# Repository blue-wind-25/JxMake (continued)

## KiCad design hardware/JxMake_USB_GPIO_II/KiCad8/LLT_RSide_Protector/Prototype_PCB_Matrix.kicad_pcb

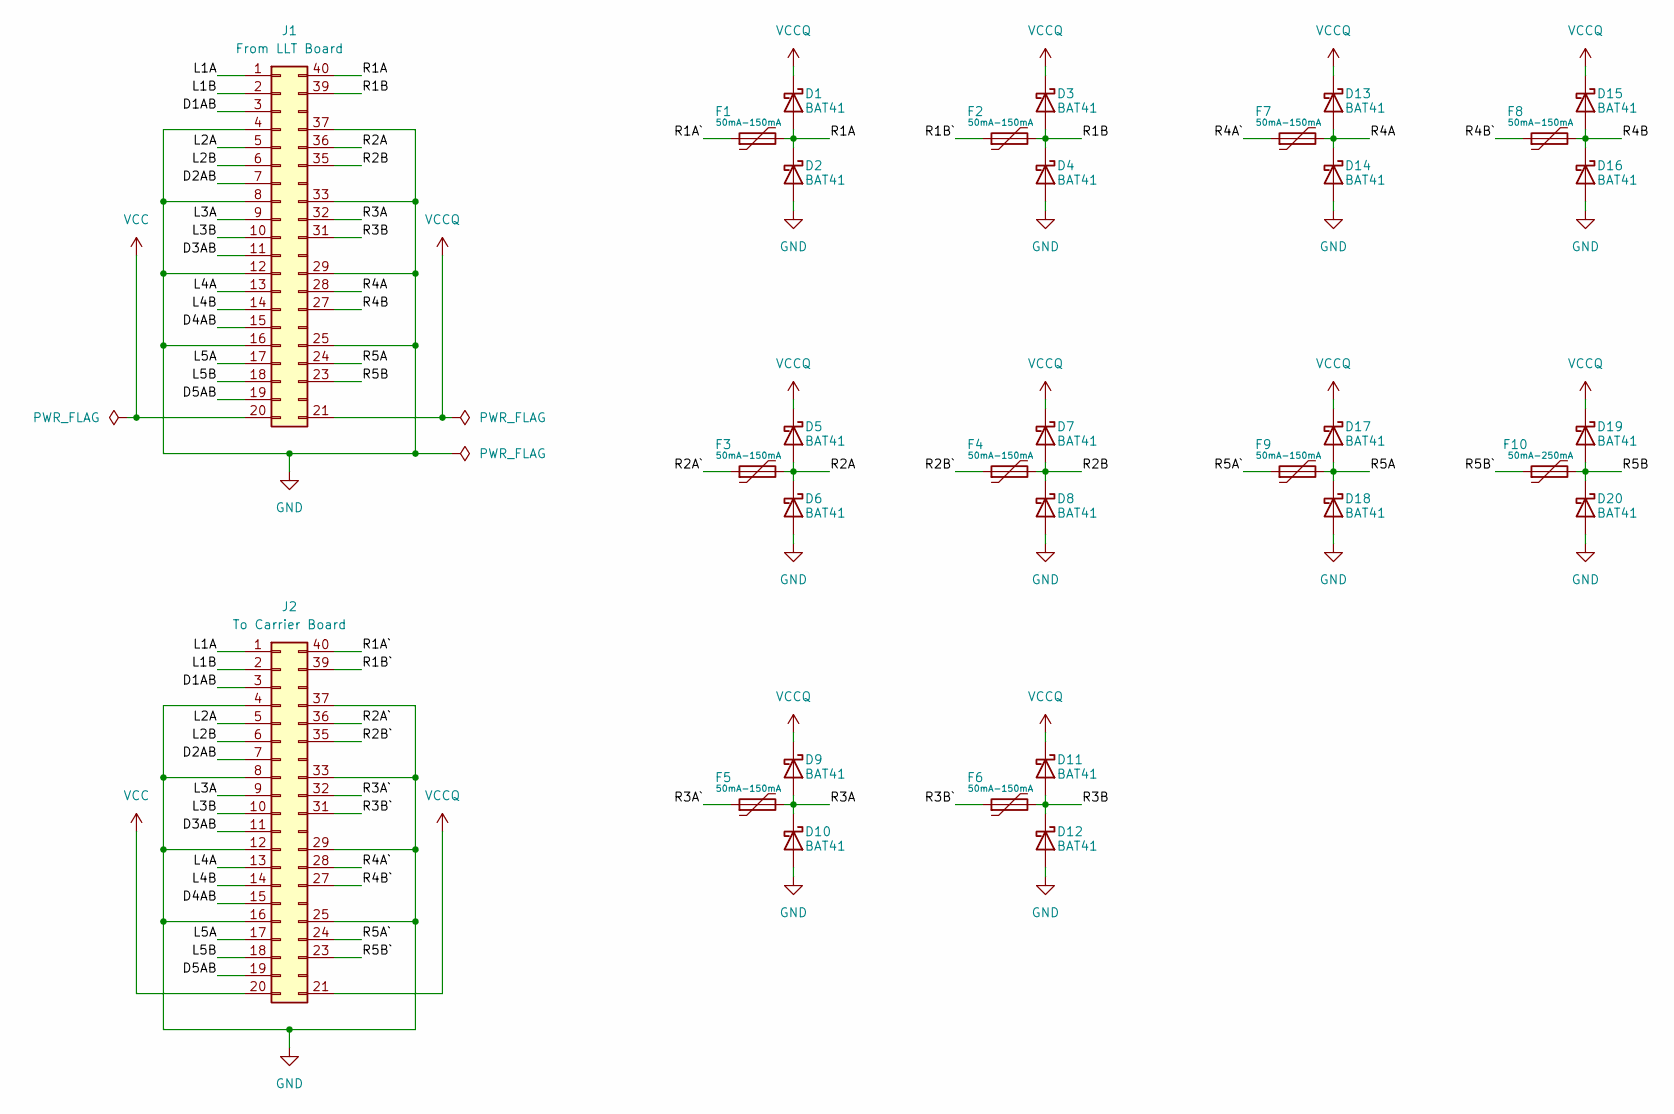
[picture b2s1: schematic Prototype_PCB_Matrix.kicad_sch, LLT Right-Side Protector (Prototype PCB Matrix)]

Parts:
D1, D2, D3, D4, D5, D6, D7, D8, D9, D10, D11, D12, D13, D14, D15, D16, D17, D18, D19, D20: BAT41; D_DO-35_SOD27_P7.62mm_Horizontal
F1, F2, F3, F4, F5, F6, F7, F8, F9: 50mA-150mA; R_1210_3225Metric_Pad1.30x2.65mm_HandSolder
F10: 50mA-250mA; R_1210_3225Metric_Pad1.30x2.65mm_HandSolder
J1: From LLT Board; DIP-40_W25.4mm_LongPads
J2: To Carrier Board; DIP-40_W25.4mm_LongPads

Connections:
/D1AB: J1.3, J2.3
/D2AB: J1.7, J2.7
/D3AB: J1.11, J2.11
/D4AB: J1.15, J2.15
/D5AB: J1.19, J2.19
/L1A: J1.1, J2.1
/L1B: J1.2, J2.2
/L2A: J1.5, J2.5
/L2B: J1.6, J2.6
/L3A: J1.9, J2.9
/L3B: J1.10, J2.10
/L4A: J1.13, J2.13
/L4B: J1.14, J2.14
/L5A: J1.17, J2.17
/L5B: J1.18, J2.18
/R1A: D1.2 (A), D2.1 (K), F1.2, J1.40
/R1A`: F1.1, J2.40
/R1B: D3.2 (A), D4.1 (K), F2.2, J1.39
/R1B`: F2.1, J2.39
/R2A: D5.2 (A), D6.1 (K), F3.2, J1.36
/R2A`: F3.1, J2.36
/R2B: D7.2 (A), D8.1 (K), F4.2, J1.35
/R2B`: F4.1, J2.35
/R3A: D9.2 (A), D10.1 (K), F5.2, J1.32
/R3A`: F5.1, J2.32
/R3B: D11.2 (A), D12.1 (K), F6.2, J1.31
/R3B`: F6.1, J2.31
/R4A: D13.2 (A), D14.1 (K), F7.2, J1.28
/R4A`: F7.1, J2.28
/R4B: D15.2 (A), D16.1 (K), F8.2, J1.27
/R4B`: F8.1, J2.27
/R5A: D17.2 (A), D18.1 (K), F9.2, J1.24
/R5A`: F9.1, J2.24
/R5B: D19.2 (A), D20.1 (K), F10.2, J1.23
/R5B`: F10.1, J2.23
GND: D2.2 (A), D4.2 (A), D6.2 (A), D8.2 (A), D10.2 (A), D12.2 (A), D14.2 (A), D16.2 (A), D18.2 (A), D20.2 (A), J1.4, J1.8, J1.12, J1.16, J1.25, J1.29, J1.33, J1.37, J2.4, J2.8, J2.12, J2.16, J2.25, J2.29, J2.33, J2.37
VCC: J1.20, J2.20
VCCQ: D1.1 (K), D3.1 (K), D5.1 (K), D7.1 (K), D9.1 (K), D11.1 (K), D13.1 (K), D15.1 (K), D17.1 (K), D19.1 (K), J1.21, J2.21

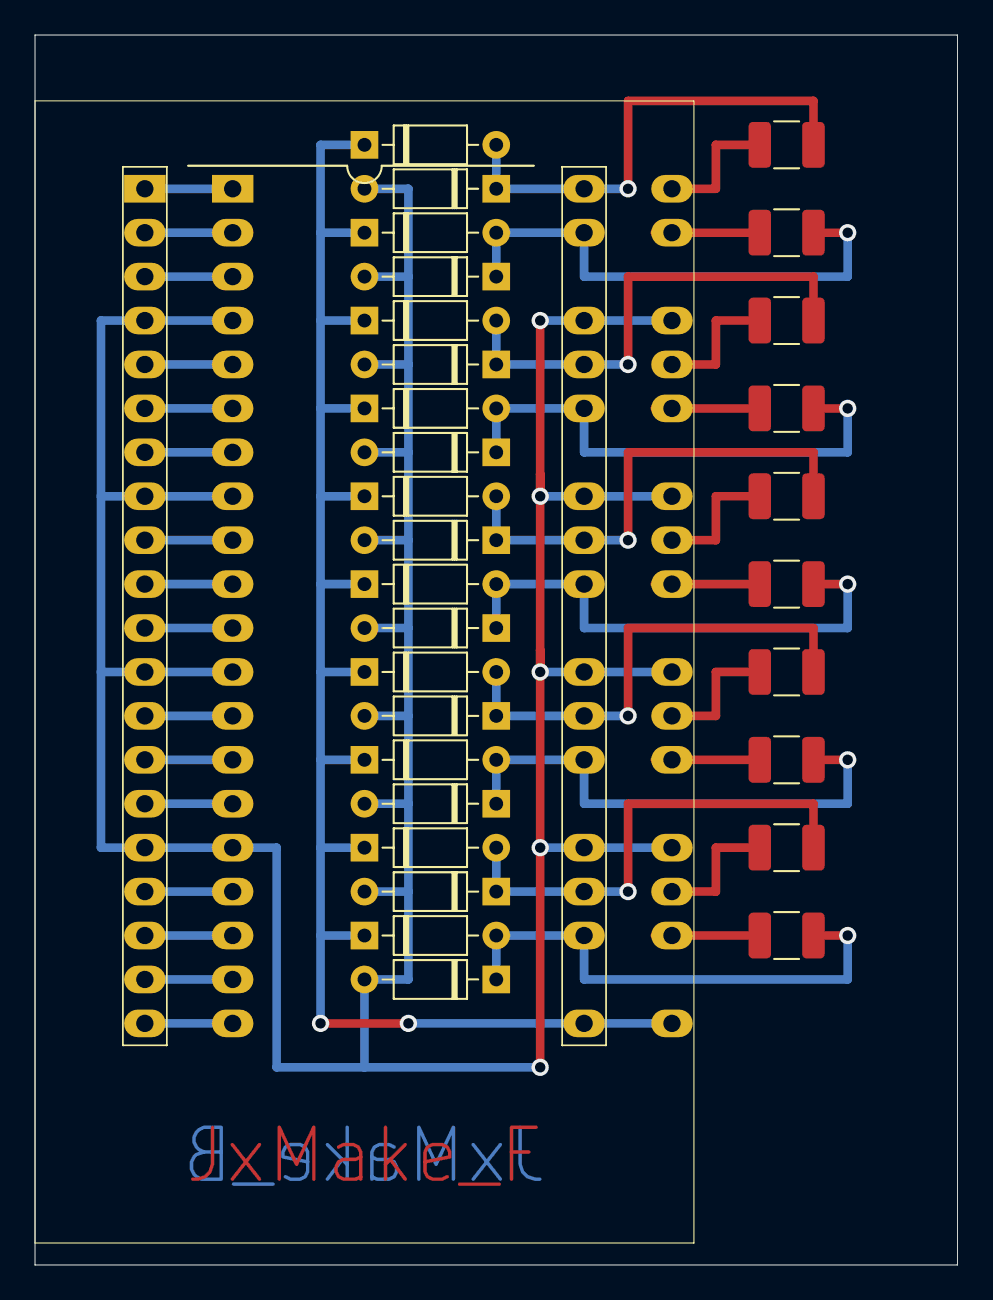
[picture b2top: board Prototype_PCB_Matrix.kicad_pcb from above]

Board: 2 copper layers, 53.3 x 71.1 mm, 32 parts (0 on the bottom side), 38 nets.

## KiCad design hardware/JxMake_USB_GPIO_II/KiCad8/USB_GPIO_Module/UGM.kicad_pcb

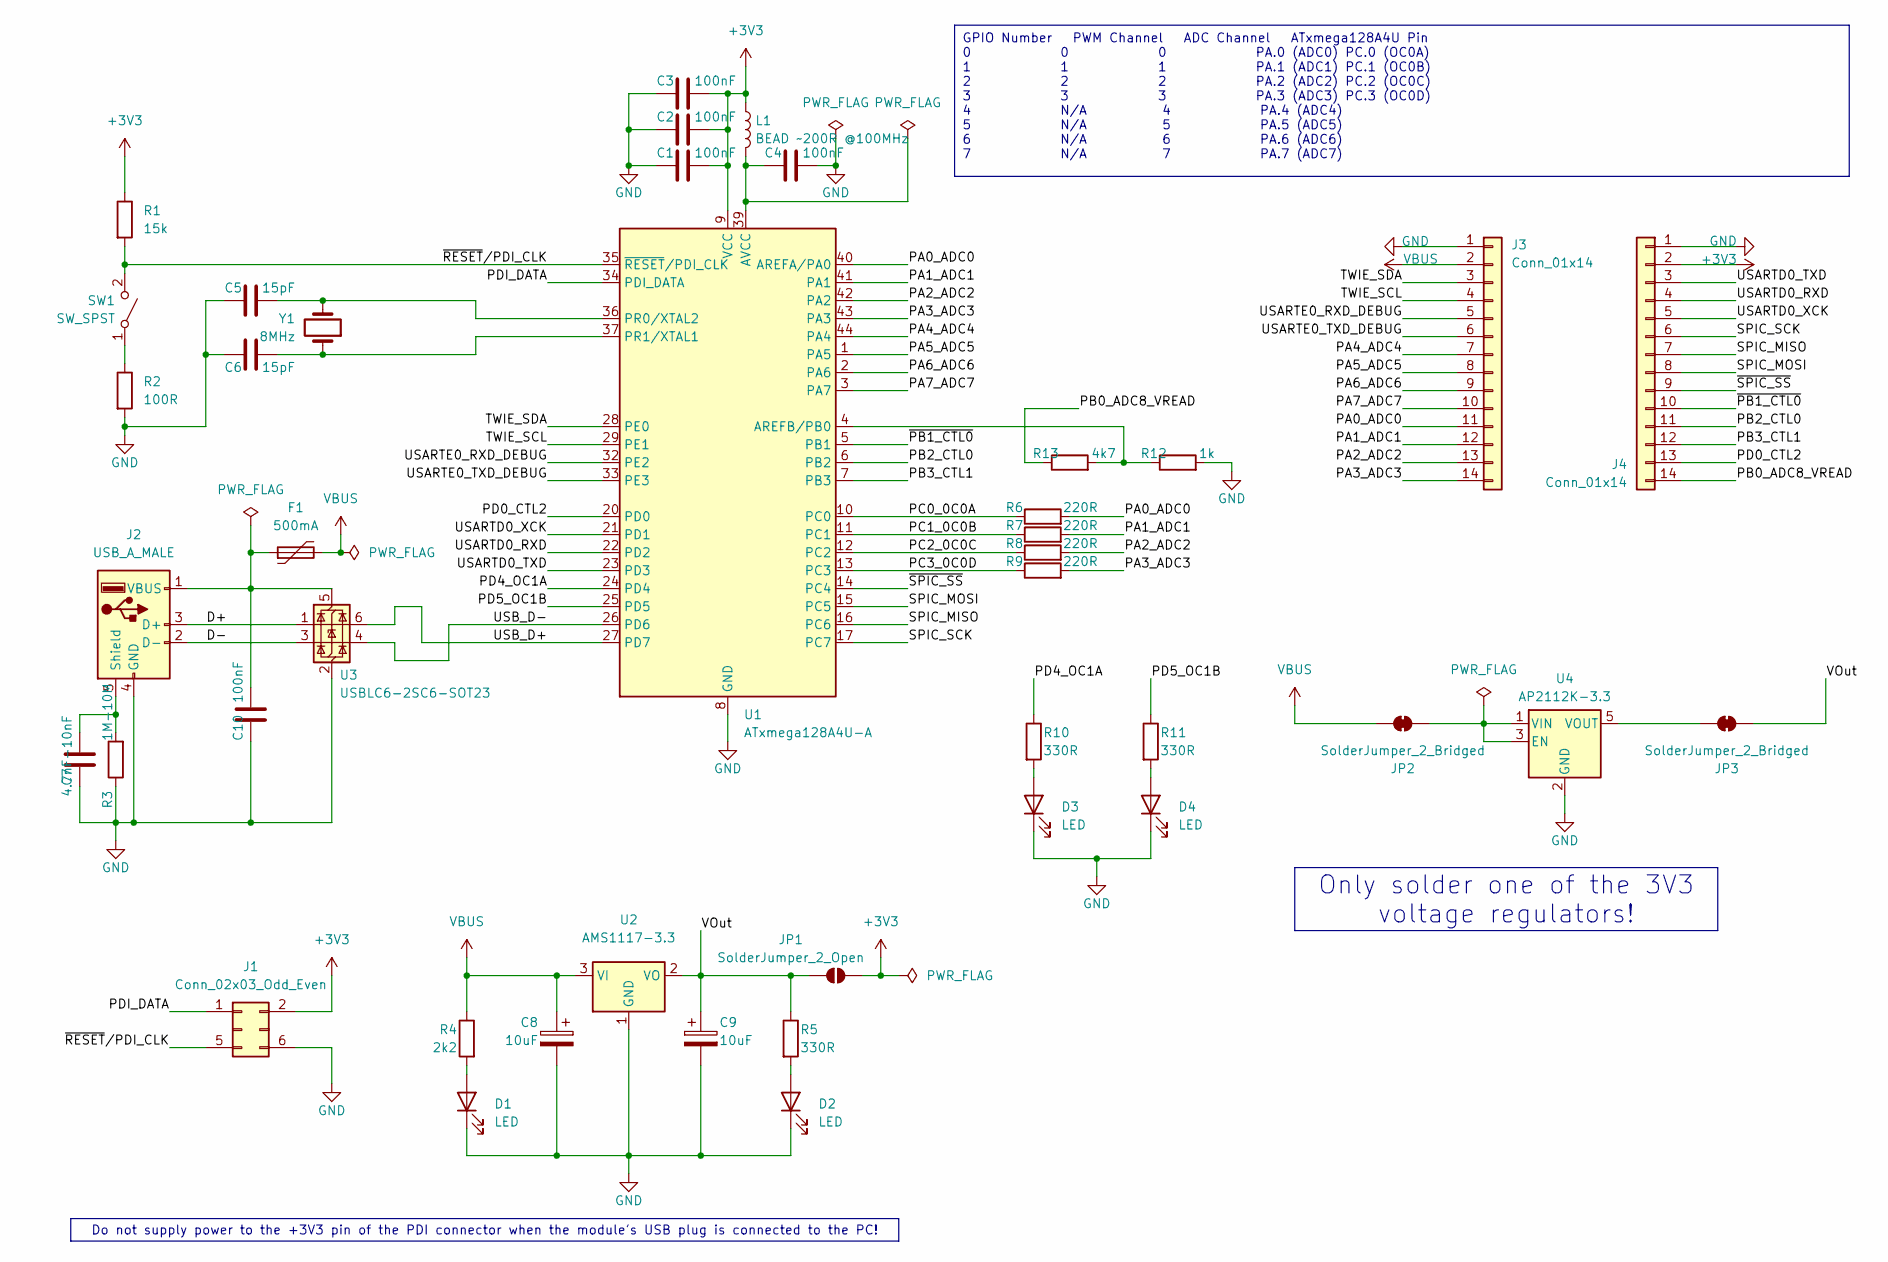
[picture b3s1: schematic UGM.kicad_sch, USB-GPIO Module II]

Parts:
C1, C2, C3, C4, C10: 100nF; C_0805_2012Metric_Pad1.18x1.45mm_HandSolder
C5, C6: 15pF; C_0805_2012Metric_Pad1.18x1.45mm_HandSolder
C7: 4.7nF-10nF; C_0805_2012Metric_Pad1.18x1.45mm_HandSolder
C8, C9: 10uF; CP_EIA-3528-21_Kemet-B_Pad1.50x2.35mm_HandSolder
D1, D2, D3, D4: LED; LED_0805_2012Metric_Pad1.15x1.40mm_HandSolder
F1: 500mA; R_1812_4532Metric_Pad1.30x3.40mm_HandSolder
J1: Conn_02x03_Odd_Even; IDC-Header_2x03_P2.54mm_Vertical
J2: USB_A_MALE; USB_A_CONNFLY_DS1095-WNR0
J3, J4: Conn_01x14; PinHeader_1x14_P2.54mm_Vertical
JP1: SolderJumper_2_Open; SolderJumper-2_P1.3mm_Open_Pad1.0x1.5mm
JP2, JP3: SolderJumper_2_Bridged; SolderJumper-2_P1.3mm_Bridged2Bar_RoundedPad1.0x1.5mm
L1: BEAD ~200R @100MHz; L_0805_2012Metric_Pad1.15x1.40mm_HandSolder
R1: 15k; R_0805_2012Metric_Pad1.20x1.40mm_HandSolder
R2: 100R; R_0805_2012Metric_Pad1.20x1.40mm_HandSolder
R3: 1M-10M; R_0805_2012Metric_Pad1.20x1.40mm_HandSolder
R4: 2k2; R_0805_2012Metric_Pad1.20x1.40mm_HandSolder
R5, R10, R11: 330R; R_0805_2012Metric_Pad1.20x1.40mm_HandSolder
R6, R7, R8, R9: 220R; R_0805_2012Metric_Pad1.20x1.40mm_HandSolder
R12: 1k; R_0805_2012Metric_Pad1.20x1.40mm_HandSolder
R13: 4k7; R_0805_2012Metric_Pad1.20x1.40mm_HandSolder
SW1: SW_SPST; SW_SPST_FSMSM
U1: ATxmega128A4U-A; TQFP-44_10x10mm_P0.8mm
U2: AMS1117-3.3; SOT-223-3_TabPin2
U3: USBLC6-2SC6-SOT23; SOT-23-6
U4: AP2112K-3.3; SOT-23-5
Y1: 8MHz; Crystal_SMD_HC49-SD_HandSoldering

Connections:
+3V3: C1.2, C2.2, C3.2, J1.2, J4.2, JP1.2 (B), L1.1, R1.1, U1.9 (VCC), U1.19 (VCC), U1.31 (VCC)
/D+: J2.3 (D+), U3.1 (I/O1)
/D-: J2.2 (D-), U3.3 (I/O2)
/PA0_ADC0: J3.11, R6.2, U1.40 (AREFA/PA0)
/PA1_ADC1: J3.12, R7.2, U1.41 (PA1)
/PA2_ADC2: J3.13, R8.2, U1.42 (PA2)
/PA3_ADC3: J3.14, R9.2, U1.43 (PA3)
/PA4_ADC4: J3.7, U1.44 (PA4)
/PA5_ADC5: J3.8, U1.1 (PA5)
/PA6_ADC6: J3.9, U1.2 (PA6)
/PA7_ADC7: J3.10, U1.3 (PA7)
/PB0_ADC8_VREAD: J4.14, R13.1
/PB2_CTL0: J4.11, U1.6 (PB2)
/PB3_CTL1: J4.12, U1.7 (PB3)
/PC0_0C0A: R6.1, U1.10 (PC0)
/PC1_0C0B: R7.1, U1.11 (PC1)
/PC2_0C0C: R8.1, U1.12 (PC2)
/PC3_0C0D: R9.1, U1.13 (PC3)
/PD0_CTL2: J4.13, U1.20 (PD0)
/PD4_OC1A: R10.1, U1.24 (PD4)
/PD5_OC1B: R11.1, U1.25 (PD5)
/PDI_DATA: J1.1, U1.34 (PDI_DATA)
/SPIC_MISO: J4.7, U1.16 (PC6)
/SPIC_MOSI: J4.8, U1.15 (PC5)
/SPIC_SCK: J4.6, U1.17 (PC7)
/TWIE_SCL: J3.4, U1.29 (PE1)
/TWIE_SDA: J3.3, U1.28 (PE0)
/USARTD0_RXD: J4.4, U1.22 (PD2)
/USARTD0_TXD: J4.3, U1.23 (PD3)
/USARTD0_XCK: J4.5, U1.21 (PD1)
/USARTE0_RXD_DEBUG: J3.5, U1.32 (PE2)
/USARTE0_TXD_DEBUG: J3.6, U1.33 (PE3)
/USB_D+: U1.27 (PD7), U3.6 (I/O1)
/USB_D-: U1.26 (PD6), U3.4 (I/O2)
/VOut: C9.1, JP1.1 (A), JP3.2 (B), R5.1, U2.2 (VO)
/~PB1_CTL0: J4.10, U1.5 (PB1)
/~RESET/PDI_CLK: J1.5, R1.2, SW1.2 (B), U1.35 (~RESET/PDI_CLK)
/~SPIC_SS: J4.9, U1.14 (PC4)
GND: C1.1, C2.1, C3.1, C4.2, C5.1, C6.1, C7.1, C8.2, C9.2, C10.1, D1.1 (K), D2.1 (K), D3.1 (K), D4.1 (K), J1.6, J2.4 (GND), J3.1, J4.1, R2.2, R3.1, R12.2, U1.8 (GND), U1.18 (GND), U1.30 (GND), U1.38 (GND), U2.1 (GND), U3.2 (GND), U4.2 (GND)
unnamed: D1.2 (A), R4.2
unnamed: D2.2 (A), R5.2
unnamed: D3.2 (A), R10.2
unnamed: D4.2 (A), R11.2
unnamed: C7.2, J2.5 (Shield), R3.2
unnamed: C10.2, F1.1, J2.1 (VBUS), U3.5 (VBUS)
unnamed: JP2.2 (B), U4.1 (VIN), U4.3 (EN)
unnamed: JP3.1 (A), U4.5 (VOUT)
unnamed: R2.1, SW1.1 (A)
unnamed: R12.1, R13.2, U1.4 (AREFB/PB0)
unnamed: C4.1, L1.2, U1.39 (AVCC)
unnamed: C5.2, U1.36 (PR0/XTAL2), Y1.2
unnamed: C6.2, U1.37 (PR1/XTAL1), Y1.1
VBUS: C8.1, F1.2, J3.2, JP2.1 (A), R4.1, U2.3 (VI)

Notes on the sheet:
GPIO Number PWM Channel ADC Channel ATxmega128A4U Pin 0 0 0 PA.0 (ADC0) PC.0 (OC0A) 1 1 1 PA.1 (ADC1) PC.1 (OC0B) 2 2 2 PA.2 (ADC2) PC.2 (OC0C) 3 3 3 PA.3 (ADC3) PC.3 (OC0D) 4 N/A 4 PA.4 (ADC4) 5 N/A 5 PA.5 (ADC5) 6 N/A 6 PA.6 (ADC6) 7 N/A 7 PA.7 (ADC7)
Do not supply power to the +3V3 pin of the PDI connector when the module's USB plug is connected to the PC!
Only solder one of the 3V3 voltage regulators!

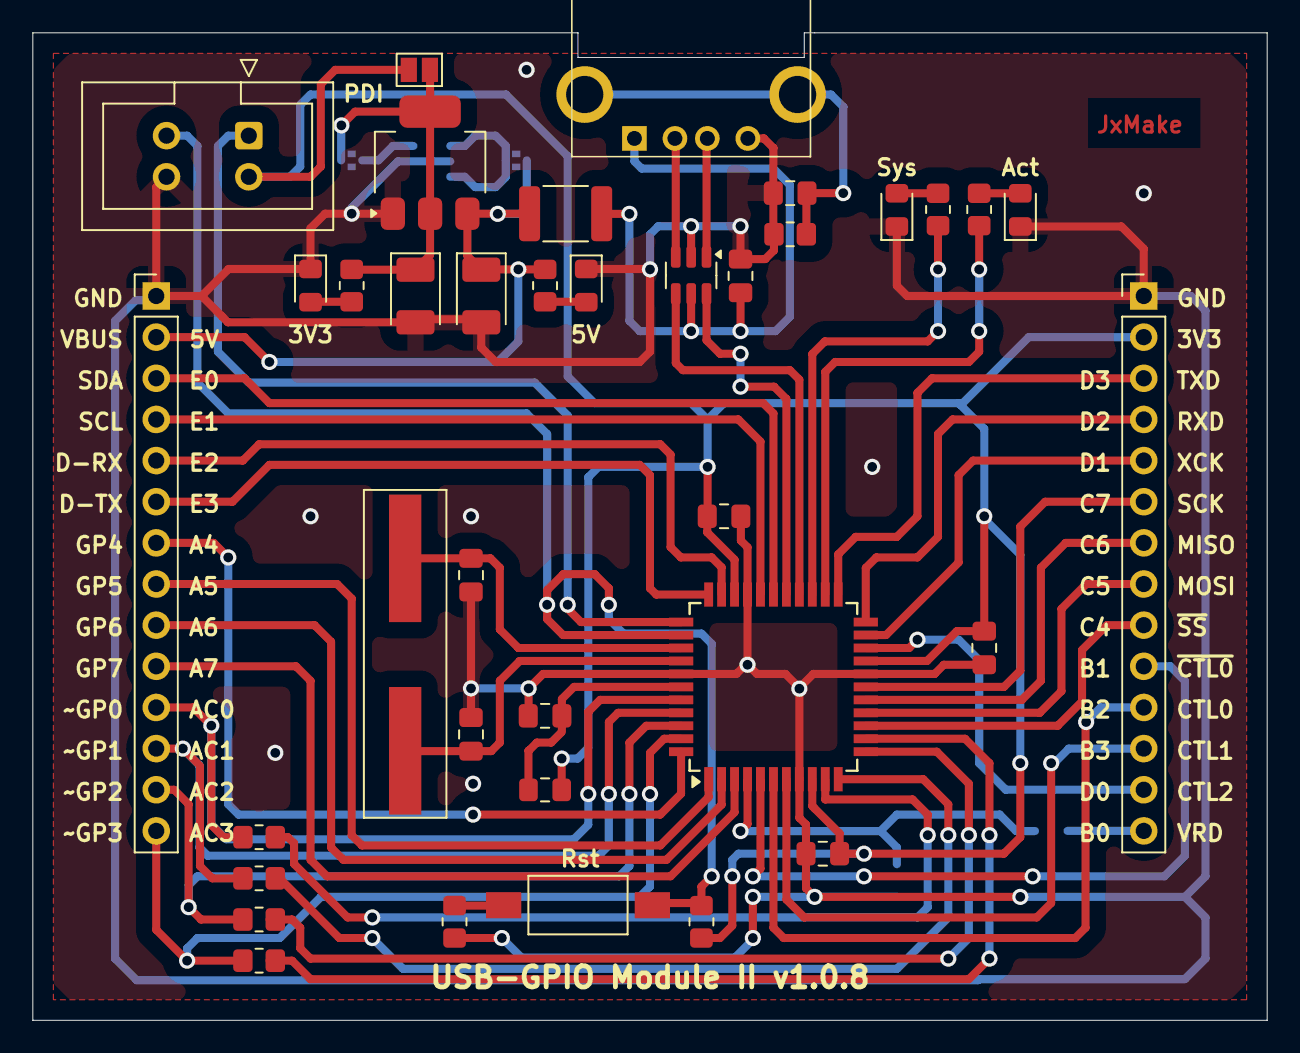
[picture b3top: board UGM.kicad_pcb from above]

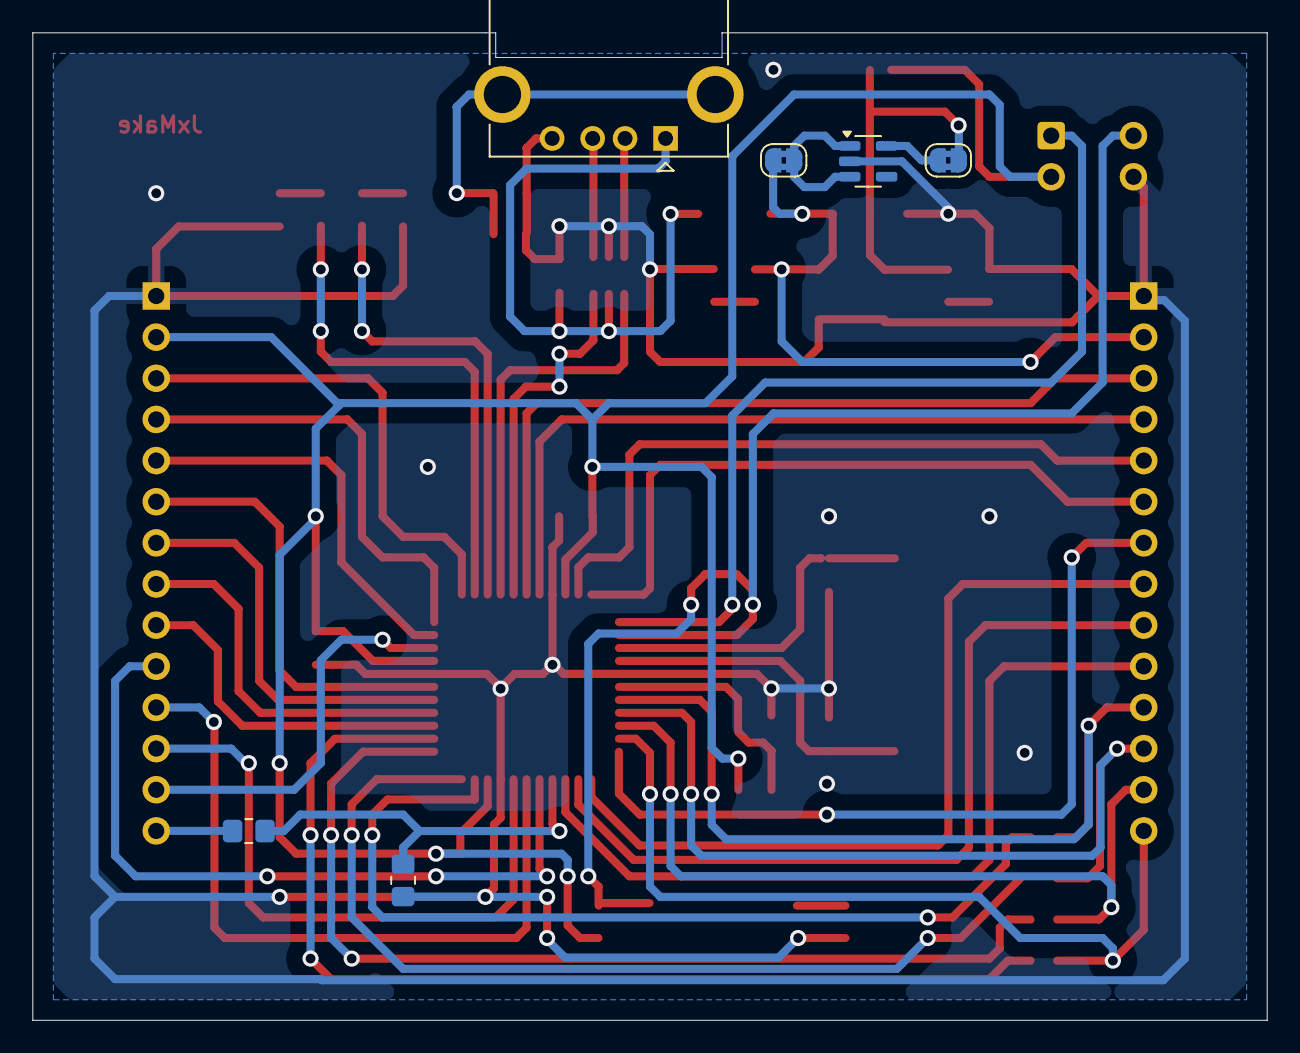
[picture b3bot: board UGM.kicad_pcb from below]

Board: 2 copper layers, 76.2 x 61.0 mm, 42 parts (6 on the bottom side), 53 nets.

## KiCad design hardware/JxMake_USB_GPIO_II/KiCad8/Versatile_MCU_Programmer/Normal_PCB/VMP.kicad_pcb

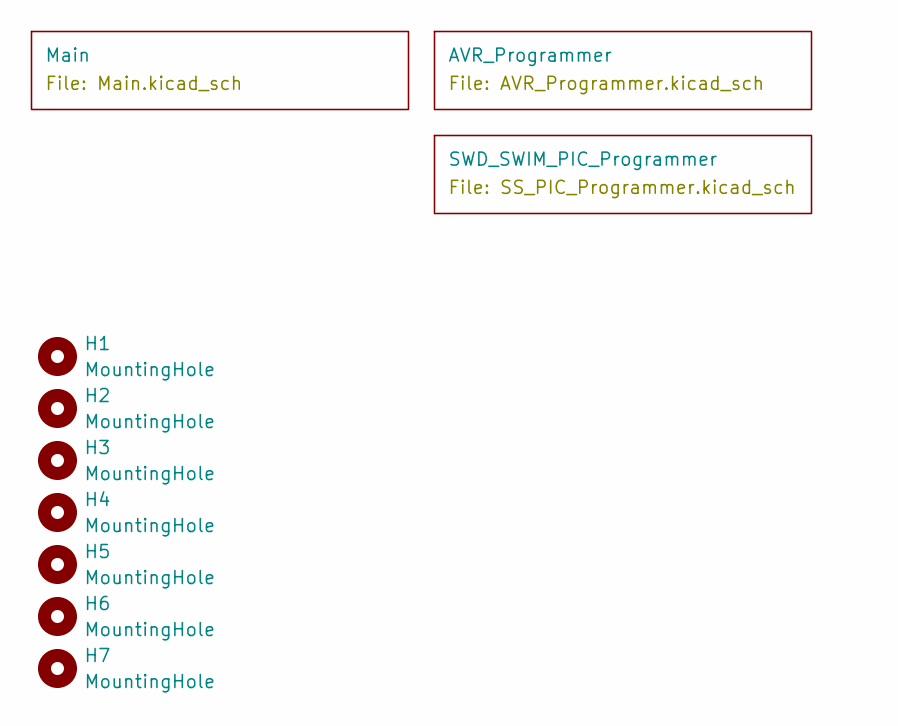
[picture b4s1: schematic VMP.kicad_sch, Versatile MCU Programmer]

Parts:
H1, H2, H3, H4, H5, H6, H7: MountingHole; MountingHole_3.2mm_M3

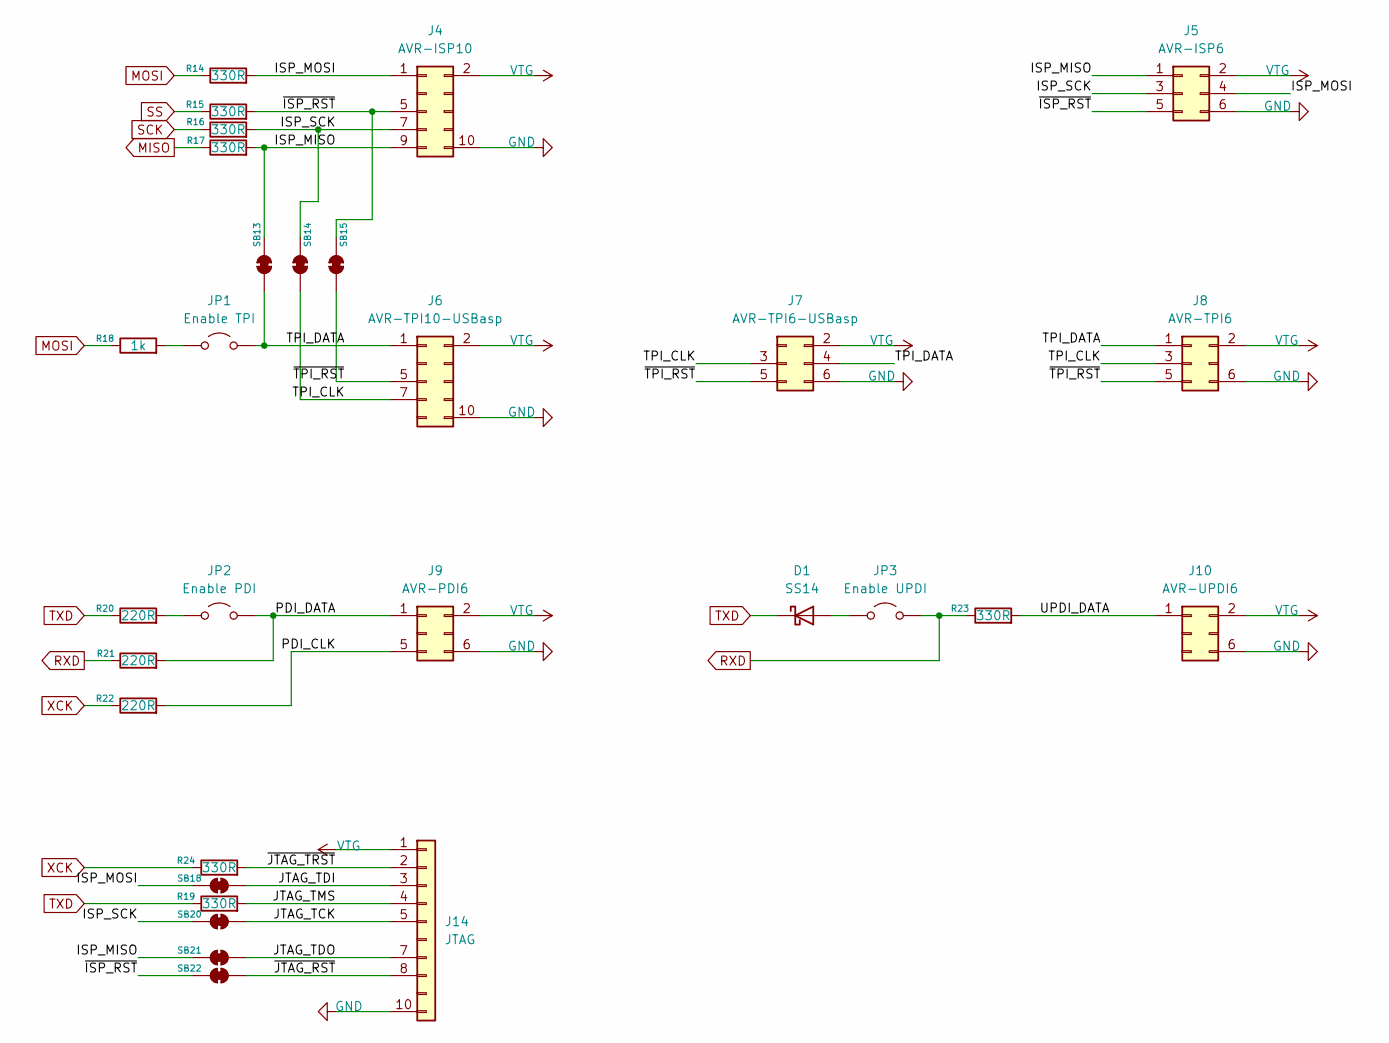
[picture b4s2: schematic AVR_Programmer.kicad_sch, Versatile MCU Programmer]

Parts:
D1: SS14; D_SMA
J4: AVR-ISP10; IDC-Header_2x05_P2.54mm_Vertical
J5: AVR-ISP6; IDC-Header_2x03_P2.54mm_Vertical
J6: AVR-TPI10-USBasp; IDC-Header_2x05_P2.54mm_Vertical
J7: AVR-TPI6-USBasp; IDC-Header_2x03_P2.54mm_Vertical
J8: AVR-TPI6; IDC-Header_2x03_P2.54mm_Vertical
J9: AVR-PDI6; IDC-Header_2x03_P2.54mm_Vertical
J10: AVR-UPDI6; IDC-Header_2x03_P2.54mm_Vertical
J14: JTAG; PinSocket_1x10_P2.54mm_Horizontal
JP1: Enable TPI; PinHeader_1x02_P2.54mm_Vertical
JP2: Enable PDI; PinHeader_1x02_P2.54mm_Vertical
JP3: Enable UPDI; PinHeader_1x02_P2.54mm_Vertical
R14, R15, R16, R17, R19, R23, R24: 330R; R_0805_2012Metric_Pad1.20x1.40mm_HandSolder
R18: 1k; R_0805_2012Metric_Pad1.20x1.40mm_HandSolder
R20, R21, R22: 220R; R_0805_2012Metric_Pad1.20x1.40mm_HandSolder
SB13, SB14, SB15, SB18, SB20, SB21, SB22: Jumper_2_Small_Bridged; SolderJumper-2_P1.3mm_Bridged_Pad1.0x1.5mm

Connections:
/AVR_Programmer/ISP_MISO: J4.9, J5.1, R17.2, SB13.1 (A), SB21.1 (A)
/AVR_Programmer/ISP_MOSI: J4.1, J5.4, R14.2, SB18.1 (A)
/AVR_Programmer/ISP_SCK: J4.7, J5.3, R16.2, SB14.1 (A), SB20.1 (A)
/AVR_Programmer/JTAG_TCK: J14.5, SB20.2 (B)
/AVR_Programmer/JTAG_TDI: J14.3, SB18.2 (B)
/AVR_Programmer/JTAG_TDO: J14.7, SB21.2 (B)
/AVR_Programmer/JTAG_TMS: J14.4, R19.2
/AVR_Programmer/PDI_CLK: J9.5, R22.2
/AVR_Programmer/PDI_DATA: J9.1, JP2.2 (B), R21.2
/AVR_Programmer/TPI_CLK: J6.7, J7.3, J8.3, SB14.2 (B)
/AVR_Programmer/TPI_DATA: J6.1, J7.4, J8.1, JP1.2 (B), SB13.2 (B)
/AVR_Programmer/UPDI_DATA: J10.1, R23.2
/AVR_Programmer/~ISP_RST: J4.5, J5.5, R15.2, SB15.1 (A), SB22.1 (A)
/AVR_Programmer/~JTAG_RST: J14.8, SB22.2 (B)
/AVR_Programmer/~JTAG_TRST: J14.2, R24.2
/AVR_Programmer/~TPI_RST: J6.5, J7.5, J8.5, SB15.2 (B)
GND: J4.10, J5.6, J6.10, J7.6, J8.6, J9.6, J10.6, J14.10; also elsewhere on the board
MISO: R17.1; also elsewhere on the board
MOSI: R14.1, R18.1; also elsewhere on the board
unnamed: D1.2 (A), JP3.1 (A)
unnamed: JP1.1 (A), R18.2
unnamed: JP2.1 (A), R20.2
RXD: JP3.2 (B), R21.1, R23.1; also elsewhere on the board
SCK: R16.1; also elsewhere on the board
SS: R15.1; also elsewhere on the board
TXD: D1.1 (K), R19.1, R20.1; also elsewhere on the board
VTG: J4.2, J5.2, J6.2, J7.2, J8.2, J9.2, J10.2, J14.1; also elsewhere on the board
XCK: R22.1, R24.1; also elsewhere on the board

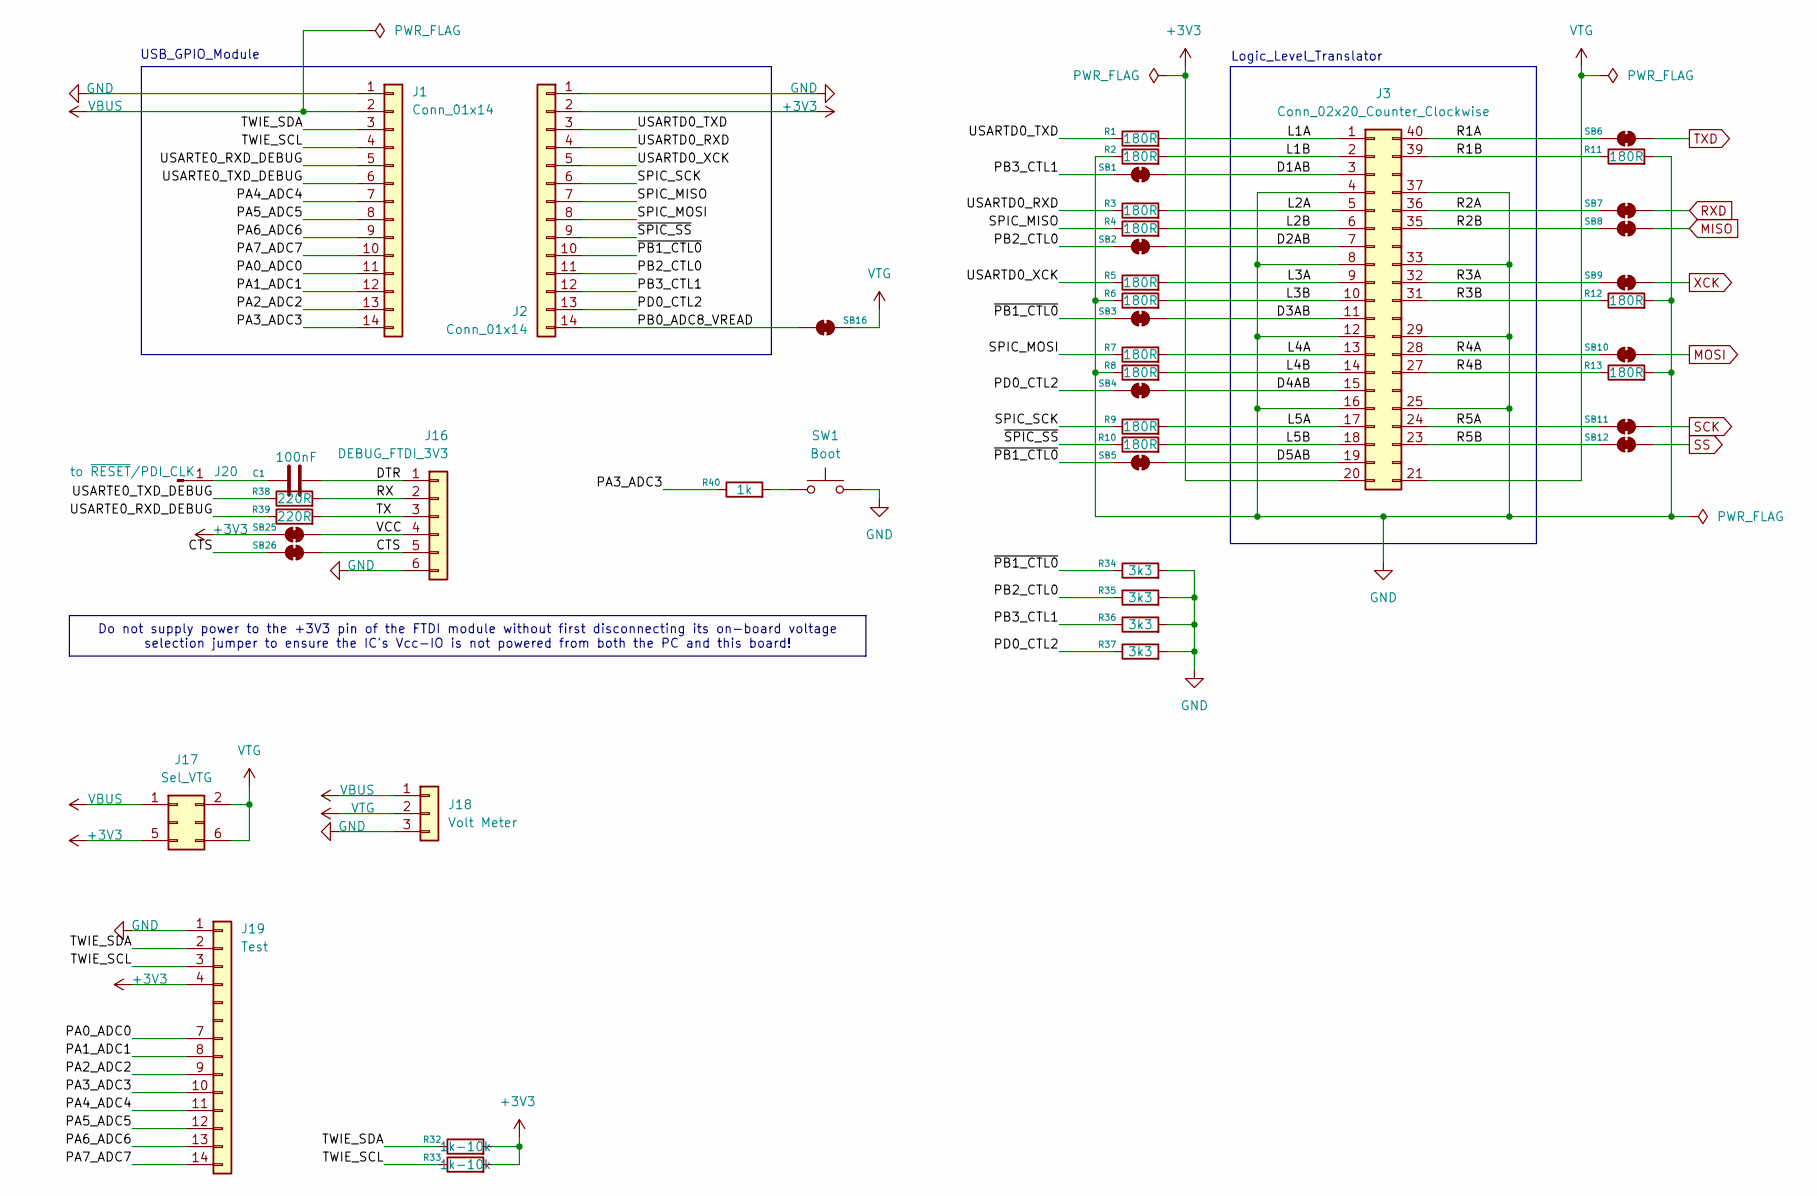
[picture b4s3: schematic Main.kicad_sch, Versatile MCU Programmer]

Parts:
C1: 100nF; C_0805_2012Metric_Pad1.18x1.45mm_HandSolder
J1, J2: Conn_01x14; PinHeader_1x14_P2.54mm_Vertical
J3: Conn_02x20_Counter_Clockwise; DIP-40_W25.4mm_LongPads
J16: DEBUG_FTDI_3V3; PinSocket_1x06_P2.54mm_Horizontal
J17: Sel_VTG; PinHeader_2x03_P2.54mm_Vertical
J18: Volt Meter; PinHeader_1x03_P2.54mm_Vertical
J19: Test; PinHeader_1x14_P2.54mm_Vertical
J20: to ~{RESET}/PDI_CLK; PinHeader_1x01_P2.54mm_Vertical
R1, R2, R3, R4, R5, R6, R7, R8, R9, R10, R11, R12, R13: 180R; R_0805_2012Metric_Pad1.20x1.40mm_HandSolder
R32, R33: 1k-10k; R_0805_2012Metric_Pad1.20x1.40mm_HandSolder
R34, R35, R36, R37: 3k3; R_0805_2012Metric_Pad1.20x1.40mm_HandSolder
R38, R39: 220R; R_0805_2012Metric_Pad1.20x1.40mm_HandSolder
R40: 1k; R_0805_2012Metric_Pad1.20x1.40mm_HandSolder
SB1, SB2, SB3, SB4, SB5, SB6, SB7, SB8, SB9, SB10, SB11, SB12, SB16, SB26: Jumper_2_Small_Bridged; SolderJumper-2_P1.3mm_Bridged_Pad1.0x1.5mm
SB25: Jumper_2_Small_Bridged; SolderJumper-2_P1.3mm_Open_Pad1.0x1.5mm
SW1: Boot; SW_SPST_FSMSM

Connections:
+3V3: J2.2, J3.20, J17.5, J19.4, R32.2, R33.2, SB25.1 (A)
/Main/CTS: J16.5, SB26.1 (A), SB26.2 (B)
/Main/D1AB: J3.3, SB1.2 (B)
/Main/D2AB: J3.7, SB2.2 (B)
/Main/D3AB: J3.11, SB3.2 (B)
/Main/D4AB: J3.15, SB4.2 (B)
/Main/D5AB: J3.19, SB5.2 (B)
/Main/DTR: C1.2, J16.1
/Main/L1A: J3.1, R1.2
/Main/L1B: J3.2, R2.2
/Main/L2A: J3.5, R3.2
/Main/L2B: J3.6, R4.2
/Main/L3A: J3.9, R5.2
/Main/L3B: J3.10, R6.2
/Main/L4A: J3.13, R7.2
/Main/L4B: J3.14, R8.2
/Main/L5A: J3.17, R9.2
/Main/L5B: J3.18, R10.2
/Main/PA0_ADC0: J1.11, J19.7
/Main/PA1_ADC1: J1.12, J19.8
/Main/PA2_ADC2: J1.13, J19.9
/Main/PA3_ADC3: J1.14, J19.10, R40.1
/Main/PA4_ADC4: J1.7, J19.11
/Main/PA5_ADC5: J1.8, J19.12
/Main/PA6_ADC6: J1.9, J19.13
/Main/PA7_ADC7: J1.10, J19.14
/Main/PB0_ADC8_VREAD: J2.14, SB16.2 (B)
/Main/PB2_CTL0: J2.11, R35.1, SB2.1 (A)
/Main/PB3_CTL1: J2.12, R36.1, SB1.1 (A)
/Main/PD0_CTL2: J2.13, R37.1, SB4.1 (A)
/Main/R1A: J3.40, SB6.1 (A)
/Main/R1B: J3.39, R11.1
/Main/R2A: J3.36, SB7.1 (A)
/Main/R2B: J3.35, SB8.1 (A)
/Main/R3A: J3.32, SB9.1 (A)
/Main/R3B: J3.31, R12.1
/Main/R4A: J3.28, SB10.1 (A)
/Main/R4B: J3.27, R13.1
/Main/R5A: J3.24, SB11.1 (A)
/Main/R5B: J3.23, SB12.1 (A)
/Main/RX: J16.2, R38.2
/Main/SPIC_MISO: J2.7, R4.1
/Main/SPIC_MOSI: J2.8, R7.1
/Main/SPIC_SCK: J2.6, R9.1
/Main/TWIE_SCL: J1.4, J19.3, R33.1
/Main/TWIE_SDA: J1.3, J19.2, R32.1
/Main/TX: J16.3, R39.2
/Main/USARTD0_RXD: J2.4, R3.1
/Main/USARTD0_TXD: J2.3, R1.1
/Main/USARTD0_XCK: J2.5, R5.1
/Main/USARTE0_RXD_DEBUG: J1.5, R39.1
/Main/USARTE0_TXD_DEBUG: J1.6, R38.1
/Main/VCC: J16.4, SB25.2 (B)
/Main/~PB1_CTL0: J2.10, R34.1, SB3.1 (A), SB5.1 (A)
/Main/~SPIC_SS: J2.9, R10.1
GND: J1.1, J2.1, J3.4, J3.8, J3.12, J3.16, J3.25, J3.29, J3.33, J3.37, J16.6, J18.3, J19.1, R2.1, R6.1, R8.1, R11.2, R12.2, R13.2, R34.2, R35.2, R36.2, R37.2, SW1.2; also elsewhere on the board
MISO: SB8.2 (B); also elsewhere on the board
MOSI: SB10.2 (B); also elsewhere on the board
unnamed: C1.1, J20.1
unnamed: R40.2, SW1.1
RXD: SB7.2 (B); also elsewhere on the board
SCK: SB11.2 (B); also elsewhere on the board
SS: SB12.2 (B); also elsewhere on the board
TXD: SB6.2 (B); also elsewhere on the board
VBUS: J1.2, J17.1, J18.1
VTG: J3.21, J17.2, J17.6, J18.2, SB16.1 (A); also elsewhere on the board
XCK: SB9.2 (B); also elsewhere on the board

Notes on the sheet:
Do not supply power to the +3V3 pin of the FTDI module without first disconnecting its on-board voltage selection jumper to ensure the IC's Vcc-IO is not powered from both the PC and this board!
Logic_Level_Translator
USB_GPIO_Module

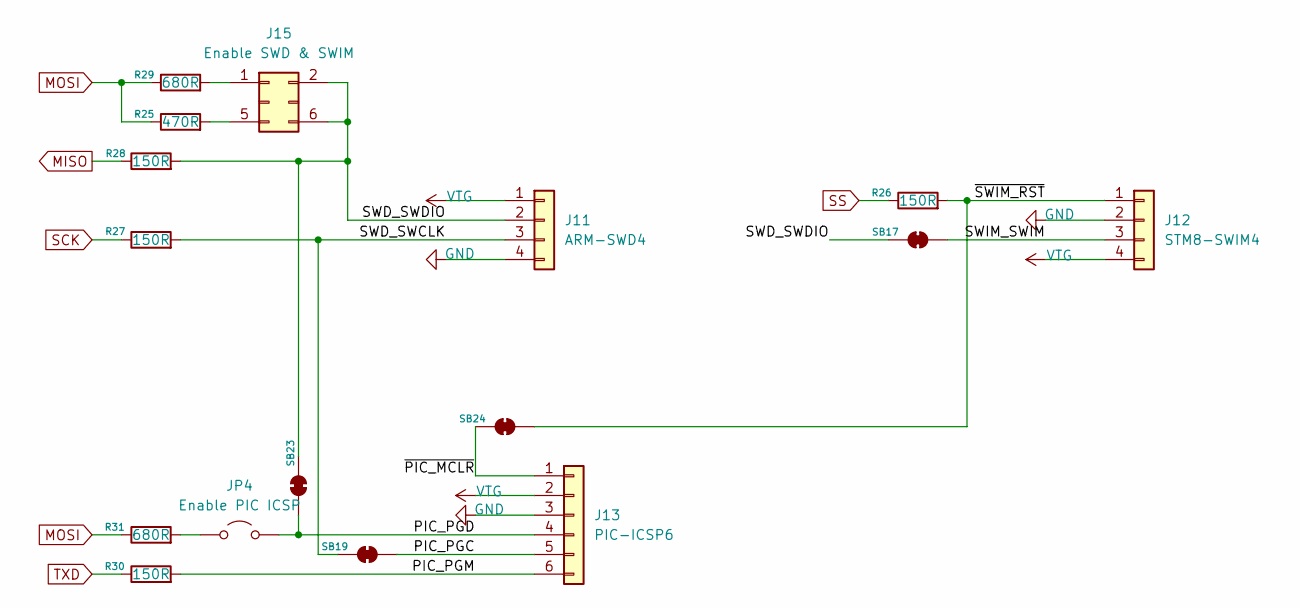
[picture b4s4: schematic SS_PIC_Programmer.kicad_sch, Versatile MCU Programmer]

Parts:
J11: ARM-SWD4; PinSocket_1x04_P2.54mm_Horizontal
J12: STM8-SWIM4; PinSocket_1x04_P2.54mm_Horizontal
J13: PIC-ICSP6; PinSocket_1x06_P2.54mm_Horizontal
J15: Enable SWD & SWIM; PinHeader_2x03_P2.54mm_Vertical
JP4: Enable PIC ICSP; PinHeader_1x02_P2.54mm_Vertical
R25: 470R; R_0805_2012Metric_Pad1.20x1.40mm_HandSolder
R26, R27, R28, R30: 150R; R_0805_2012Metric_Pad1.20x1.40mm_HandSolder
R29, R31: 680R; R_0805_2012Metric_Pad1.20x1.40mm_HandSolder
SB17, SB19, SB23, SB24: Jumper_2_Small_Bridged; SolderJumper-2_P1.3mm_Bridged_Pad1.0x1.5mm

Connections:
/SWD_SWIM_PIC_Programmer/PIC_PGC: J13.5, SB19.2 (B)
/SWD_SWIM_PIC_Programmer/PIC_PGD: J13.4, JP4.2 (B), SB23.2 (B)
/SWD_SWIM_PIC_Programmer/PIC_PGM: J13.6, R30.2
/SWD_SWIM_PIC_Programmer/SWD_SWCLK: J11.3, R27.2, SB19.1 (A)
/SWD_SWIM_PIC_Programmer/SWD_SWDIO: J11.2, J15.2, J15.6, R28.2, SB17.1 (A), SB23.1 (A)
/SWD_SWIM_PIC_Programmer/SWIM_SWIM: J12.3, SB17.2 (B)
/SWD_SWIM_PIC_Programmer/~PIC_MCLR: J13.1, SB24.1 (A)
/SWD_SWIM_PIC_Programmer/~SWIM_RST: J12.1, R26.2, SB24.2 (B)
GND: J11.4, J12.2, J13.3; also elsewhere on the board
MISO: R28.1; also elsewhere on the board
MOSI: R25.1, R29.1, R31.1; also elsewhere on the board
unnamed: J15.1, R29.2
unnamed: J15.5, R25.2
unnamed: JP4.1 (A), R31.2
SCK: R27.1; also elsewhere on the board
SS: R26.1; also elsewhere on the board
TXD: R30.1; also elsewhere on the board
VTG: J11.1, J12.4, J13.2; also elsewhere on the board
